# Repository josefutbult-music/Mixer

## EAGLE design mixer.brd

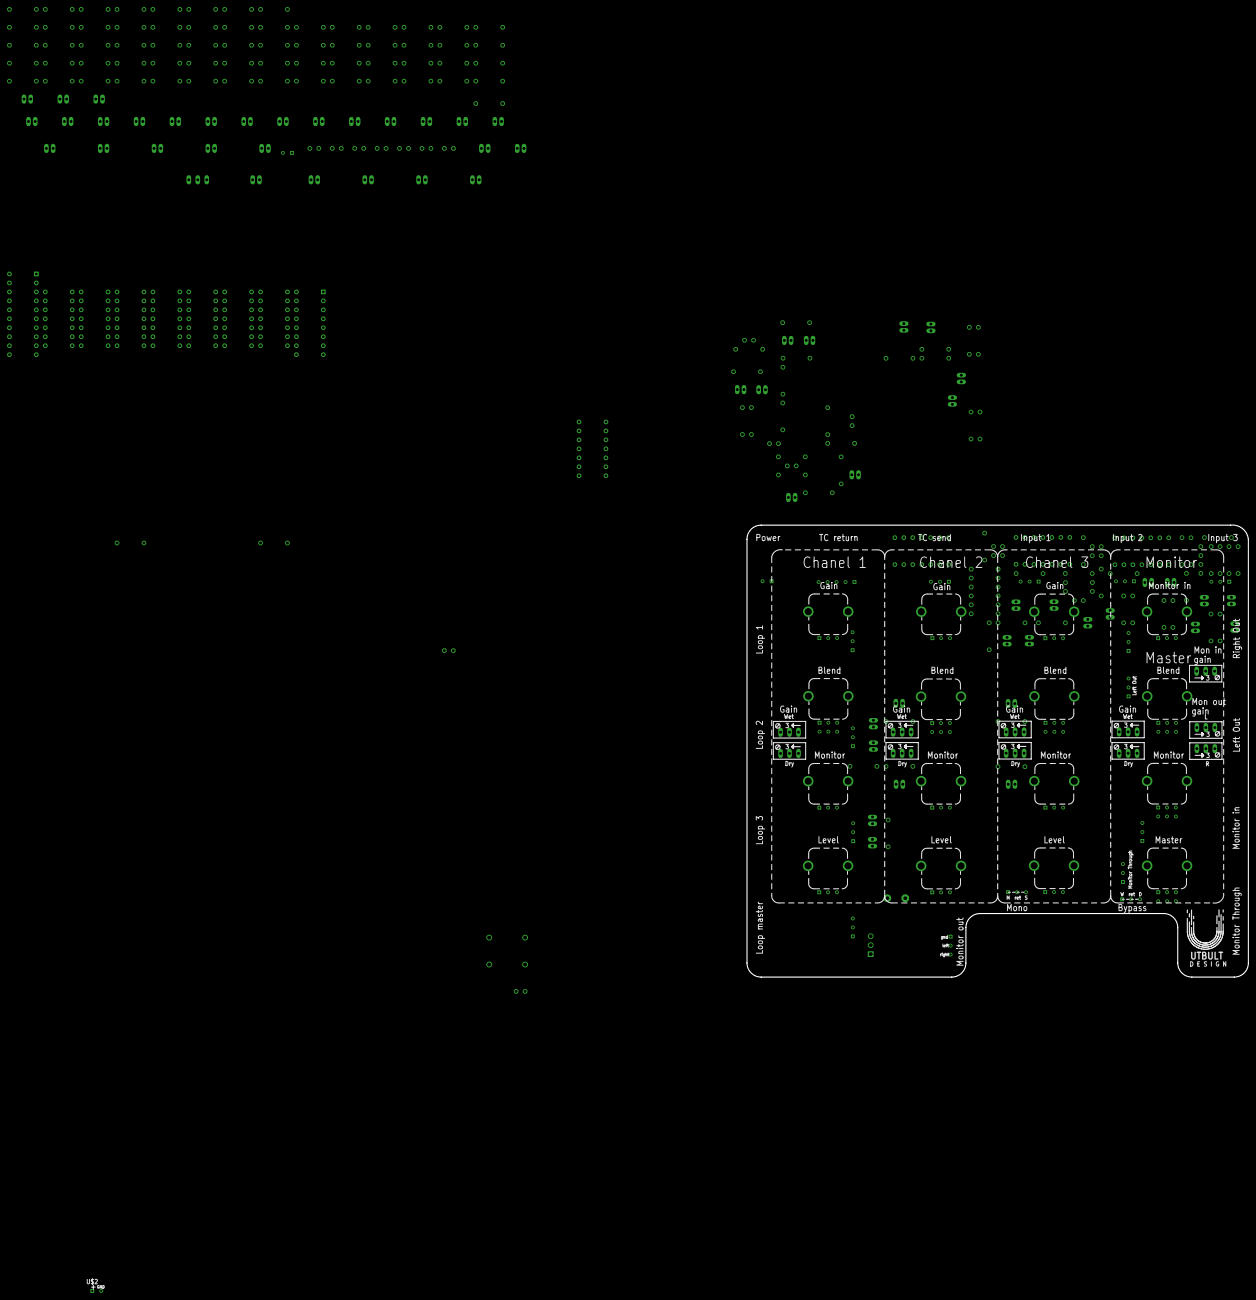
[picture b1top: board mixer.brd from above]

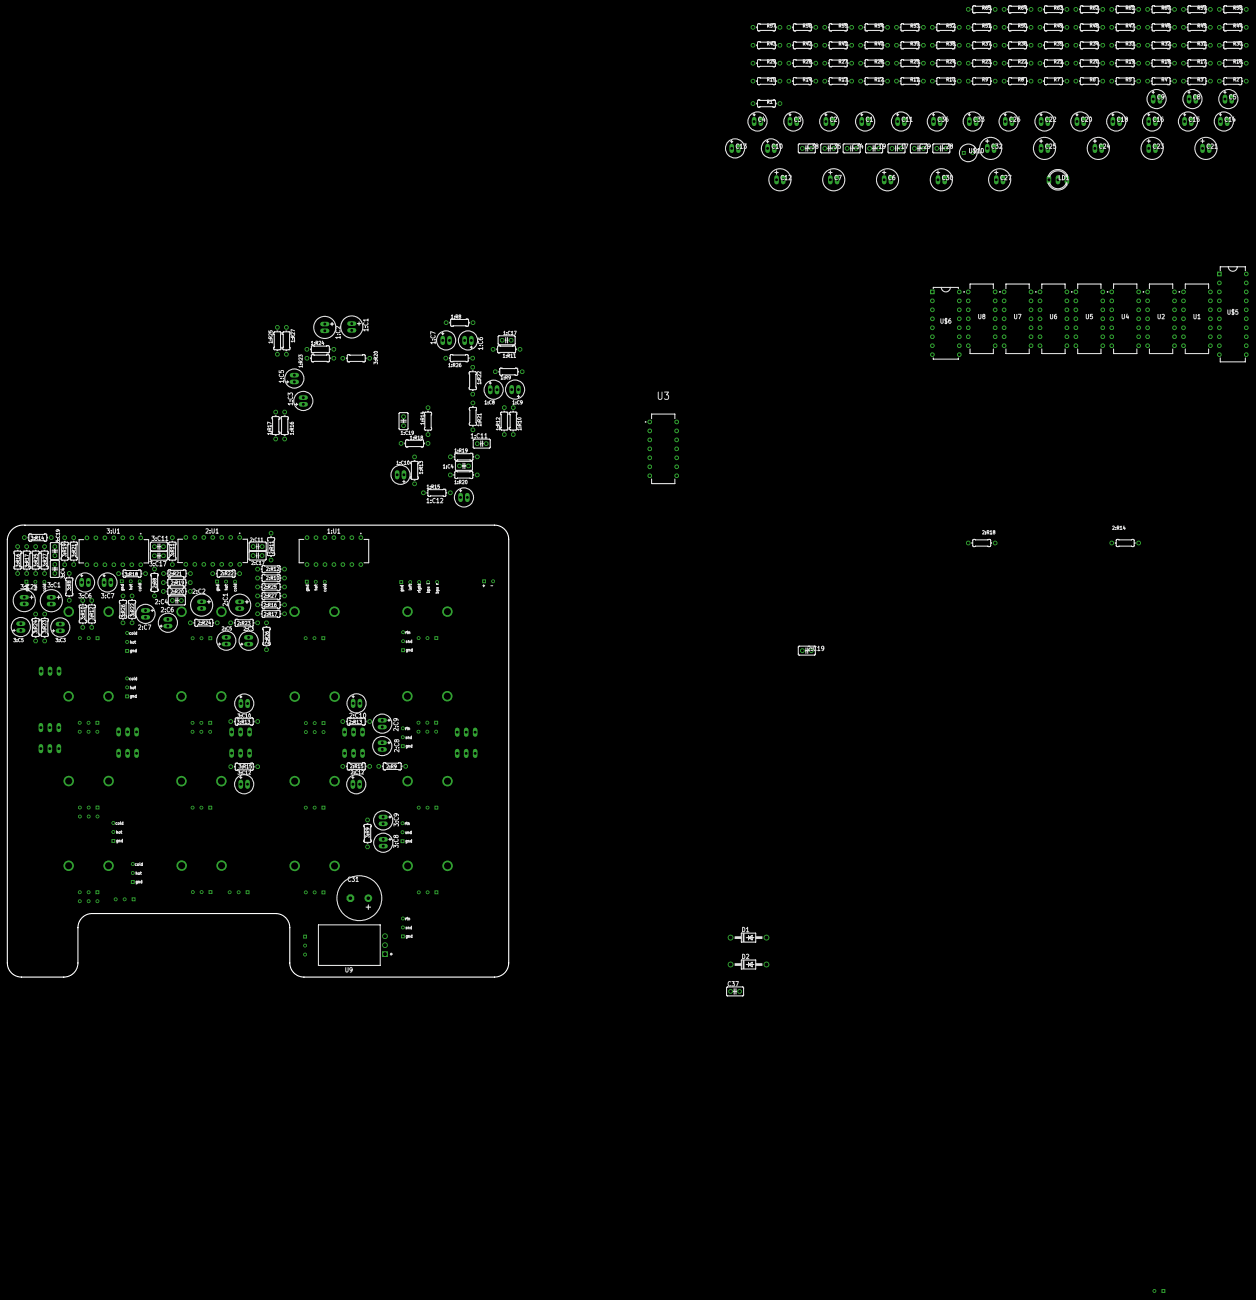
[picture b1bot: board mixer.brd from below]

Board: 2 copper layers, 142.0 x 128.0 mm, 269 parts (237 on the bottom side), 199 nets, no tracks yet.

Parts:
1:BLEND, 2:BLEND, 3:BLEND: 50 k; RK09L124000Z
1:C1, 1:C2, 2:C1, 2:C2, 3:C1, 3:C2: 10u, 63V; E2,0-6
1:C3, 1:C5, 1:C6, 1:C7, 1:C8, 1:C9, 1:C10, 1:C12, 2:C3, 2:C5, 2:C6, 2:C7, 2:C8, 2:C9, 2:C10, 2:C12, 3:C3, 3:C5, 3:C6, 3:C7, 3:C8, 3:C9, 3:C10, 3:C12: 10u; E2,0-5
1:C4, 1:C17, 1:C19, 2:C4, 2:C17, 2:C19, 3:C4, 3:C17, 3:C19: 18 p; C025-025X050
1:C11, 2:C11, 3:C11: 100 n; C025-025X050
1:GAIN, 2:GAIN, 3:GAIN: 10 k; RK09L1140
1:GAIN1, 1:GAIN2, 2:GAIN1, 2:GAIN2, 3:GAIN1, 3:GAIN2: 500 k; RJ9W
1:IN, 2:IN, 3:IN: HOT_COLD
1:LEVEL, 2:LEVEL, 3:LEVEL: RK09L1140
1:R8, 1:R9, 1:R10, 1:R16, 1:R17, 1:R23, 1:R24, 2:R8, 2:R9, 2:R10, 2:R16, 2:R17, 2:R23, 2:R24, 3:R8, 3:R9, 3:R10, 3:R16, 3:R17, 3:R23, 3:R24: 100 k; 0204/7
1:R11, 1:R14, 2:R11, 2:R14, 3:R11, 3:R14: 47 k; 0204/7
1:R12, 1:R18, 1:R26, 2:R12, 2:R18, 2:R26, 3:R12, 3:R18, 3:R26: 1 k; 0204/7
1:R13, 1:R15, 2:R13, 2:R15, 3:R13, 3:R15: 2.2 k; 0204/7
1:R19, 1:R20, 1:R21, 1:R22, 2:R19, 2:R20, 2:R21, 2:R22, 3:R19, 3:R20, 3:R21, 3:R22: 10 k; 0204/7
1:R25, 1:R27, 2:R25, 2:R27, 3:R25, 3:R27: 4.7 k; 0204/7
1:U1, 2:U1, 3:U1: TL074; DIP762W53P254L1969H508Q14B
1:U2, 2:U2, 3:U2: SEND_RETURN; SND_RET
BLEND1: 50 k; RK09L124000Z
BYPASS: BUTTON; 3-HOLES
C1, C2, C3, C4, C5, C8, C9, C10, C11, C13, C14, C15, C16, C18, C20, C22, C26, C33, C36: 10u; E2,0-5
C6, C7, C12, C21, C23, C24, C25, C32: 10u, 63V; E2,0-6
C17, C19, C34, C35, C38: 18 p; C025-025X050
C27, C30: 2.2u, 63V; E2,0-6
C28, C29, C37: 100 n; C025-025X050
C31: 390 u / 63 V; E5,0-12,5
D1, D2: 1N4004; DO41-10
GAIN1, GAIN2, GAIN3, GAIN4: 500 k; RJ9W
GAIN5: 10 k; RJ9W
LD1: DUOLED-A-5MM
LOOPMASTER: SEND_RETURN; SND_RET
MONO: BUTTON; 3-HOLES
MON_IN: HOT_COLD
MON_OUT: LEFT_RIGHT
MON_THROUGH: HOT_COLD
OUT_L: HOT_COLD
OUT_R: HOT_COLD
PWR$1: PWR
R1, R2, R3, R4, R6, R21, R22, R25, R26, R27, R32, R33, R34, R35, R36, R45, R46, R51, R52, R53, R54, R64, R65: 10 k; 0204/7
R5, R7, R28, R29, R37, R38: 100; 0204/7
R8, R9, R10, R16, R17, R19, R20, R23, R24, R30, R31, R39, R40, R47, R48, R49, R50: 100 k; 0204/7
R11, R14, R55, R61: 47 k; 0204/7
R12, R18, R56, R60, R63: 1 k; 0204/7
R13, R15, R59, R62: 2.2 k; 0204/7
R41, R42, R43, R44, R57, R58: 4.7 k; 0204/7
TC_RET: LEFT_RIGHT_BYPASS
TC_SEND_JACK: HOT_COLD
U1, U2, U3, U4, U5, U6, U7, U8: TL074; DIP762W53P254L1969H508Q14B
U9: V7809W-500R; CONV_V7809W-500R
U$1: UTBULT_DESIGN3; UD_3
U$2: UNBALANCED_INPUT_JACK; BALANCED_INPUT_JACK
U$5: ADG333ABNZADG333ABNZ; DIP762W53P254L2591H508Q20B
U$6: ADG436BNZADG436BNZ; DIP762W53P254L2006H508Q16B
U$10: SBC1-102-211
VOLUM6: 50 k; RK09L124000Z
VOLUME1: 50 k; RK09L124000Z
VOLUME2, VOLUME3, VOLUME4, VOLUME5: 10 k; RK09L1140

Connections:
1:COLD_IN: 1:C1.+, 1:IN.P$3, 1:R27.2
1:COLD_SEND: 1:C3.+, 1:R16.2, 1:U1.10
1:HOT_IN: 1:C2.+, 1:IN.P$2, 1:R25.2
1:HOT_SEND: 1:C5.+, 1:R17.2, 1:U1.12
1:N$1: 1:C10.+, 1:R13.2
1:N$2: 1:C12.+, 1:R15.2
1:N$3: 1:GAIN1.A, 1:GAIN1.S, 1:R13.1
1:N$4: 1:GAIN2.A, 1:GAIN2.S, 1:R15.1
1:N$9: 1:GAIN.P$3, 1:R19.2, 1:R20.2, 1:R21.1, 1:U1.8, 1:U1.9
1:N$11: 1:C4.1, 1:R19.1
1:N$12: 1:C4.2, 1:R20.1, 1:R22.2, 1:R26.1, 1:U1.13
1:N$14: 1:C1.-, 1:C3.-, 1:R23.2
1:N$15: 1:C2.-, 1:C5.-, 1:R24.2
1:N$17: 1:GAIN.P$2, 1:R26.2
1:N$23: 1:C6.-, 1:C7.-, 1:R8.2
1:N$24: 1:C11.1, 1:U1.11
1:N$25: 1:C6.+, 1:U2.P$3
1:N$26: 1:C8.-, 1:C9.-, 1:R9.2
1:N$27: 1:C8.+, 1:U2.P$2
1:N$28: 1:C9.+, 1:R10.2, 1:R12.2
1:N$29: 1:C17.2, 1:GAIN1.E, 1:R11.2, 1:U1.2
1:N$30: 1:C19.2, 1:GAIN2.E, 1:R14.2, 1:U1.6
1:N$33: 1:R12.1, 1:U1.3
1:N$36: 1:R18.1, 1:U1.5
1:N$37: 1:BLEND.P$8, 1:C19.1, 1:R14.1, 1:U1.7
1:SND_RET_OUT: 1:BLEND.P$1, 1:C17.1, 1:R11.1, 1:U1.1
2:COLD_IN: 2:C1.+, 2:IN.P$3, 2:R27.2
2:COLD_SEND: 2:C3.+, 2:R16.2, 2:U1.10
2:HOT_IN: 2:C2.+, 2:IN.P$2, 2:R25.2
2:HOT_SEND: 2:C5.+, 2:R17.2, 2:U1.12
2:N$1: 2:C10.+, 2:R13.2
2:N$2: 2:C12.+, 2:R15.2
2:N$3: 2:GAIN1.A, 2:GAIN1.S, 2:R13.1
2:N$4: 2:GAIN2.A, 2:GAIN2.S, 2:R15.1
2:N$9: 2:GAIN.P$3, 2:R19.2, 2:R20.2, 2:R21.1, 2:U1.8, 2:U1.9
2:N$11: 2:C4.1, 2:R19.1
2:N$12: 2:C4.2, 2:R20.1, 2:R22.2, 2:R26.1, 2:U1.13
2:N$14: 2:C1.-, 2:C3.-, 2:R23.2
2:N$15: 2:C2.-, 2:C5.-, 2:R24.2
2:N$17: 2:GAIN.P$2, 2:R26.2
2:N$23: 2:C6.-, 2:C7.-, 2:R8.2
2:N$24: 2:C11.1, 2:U1.11
2:N$25: 2:C6.+, 2:U2.P$3
2:N$26: 2:C8.-, 2:C9.-, 2:R9.2
2:N$27: 2:C8.+, 2:U2.P$2
2:N$28: 2:C9.+, 2:R10.2, 2:R12.2
2:N$29: 2:C17.2, 2:GAIN1.E, 2:R11.2, 2:U1.2
2:N$30: 2:C19.2, 2:GAIN2.E, 2:R14.2, 2:U1.6
2:N$33: 2:R12.1, 2:U1.3
2:N$36: 2:R18.1, 2:U1.5
2:N$37: 2:BLEND.P$8, 2:C19.1, 2:R14.1, 2:U1.7
2:SND_RET_OUT: 2:BLEND.P$1, 2:C17.1, 2:R11.1, 2:U1.1
3:COLD_IN: 3:C1.+, 3:IN.P$3, 3:R27.2
3:COLD_SEND: 3:C3.+, 3:R16.2, 3:U1.10
3:HOT_IN: 3:C2.+, 3:IN.P$2, 3:R25.2
3:HOT_SEND: 3:C5.+, 3:R17.2, 3:U1.12
3:N$1: 3:C10.+, 3:R13.2
3:N$2: 3:C12.+, 3:R15.2
3:N$3: 3:GAIN1.A, 3:GAIN1.S, 3:R13.1
3:N$4: 3:GAIN2.A, 3:GAIN2.S, 3:R15.1
3:N$9: 3:GAIN.P$3, 3:R19.2, 3:R20.2, 3:R21.1, 3:U1.8, 3:U1.9
3:N$11: 3:C4.1, 3:R19.1
3:N$12: 3:C4.2, 3:R20.1, 3:R22.2, 3:R26.1, 3:U1.13
3:N$14: 3:C1.-, 3:C3.-, 3:R23.2
3:N$15: 3:C2.-, 3:C5.-, 3:R24.2
3:N$17: 3:GAIN.P$2, 3:R26.2
3:N$23: 3:C6.-, 3:C7.-, 3:R8.2
3:N$24: 3:C11.1, 3:U1.11
3:N$25: 3:C6.+, 3:U2.P$3
3:N$26: 3:C8.-, 3:C9.-, 3:R9.2
3:N$27: 3:C8.+, 3:U2.P$2
3:N$28: 3:C9.+, 3:R10.2, 3:R12.2
3:N$29: 3:C17.2, 3:GAIN1.E, 3:R11.2, 3:U1.2
3:N$30: 3:C19.2, 3:GAIN2.E, 3:R14.2, 3:U1.6
3:N$33: 3:R12.1, 3:U1.3
3:N$36: 3:R18.1, 3:U1.5
3:N$37: 3:BLEND.P$8, 3:C19.1, 3:R14.1, 3:U1.7
3:SND_RET_OUT: 3:BLEND.P$1, 3:C17.1, 3:R11.1, 3:U1.1
+9V: 1:C11.2, 1:U1.4, 2:C11.2, 2:U1.4, 3:C11.2, 3:U1.4, C29.1, D1.C, D2.C, R45.1, R64.2, R65.1, U1.4, U2.4, U3.4, U4.4, U5.4, U6.4, U7.4, U8.4, U$5.VDD, U$6.VDD
+48V: 1:R25.1, 1:R27.1, 2:R25.1, 2:R27.1, 3:R25.1, 3:R27.1, C30.+, C31.+, R41.1, R42.1, R43.1, R44.1, R57.1, R58.1, U$10.P$2
COLD_SEND: C11.+, R47.2, U4.3
DRY1: 1:C7.+, 1:R18.2, 1:R22.1, 1:U1.14, U$5.S1B, VOLUME2.P$3
DRY2: 2:C7.+, 2:R18.2, 2:R22.1, 2:U1.14, U$5.S2B, VOLUME3.P$3
DRY3: 3:C7.+, 3:R18.2, 3:R22.1, 3:U1.14, U$5.S3B, VOLUME4.P$3
GND: 1:BLEND.P$4, 1:BLEND.P$5, 1:C10.-, 1:C12.-, 1:GAIN.P$4, 1:GAIN.P$5, 1:IN.P$1, 1:LEVEL.P$4, 1:LEVEL.P$5, 1:R8.1, 1:R9.1, 1:R23.1, 1:R24.1, 1:U2.P$1, 2:BLEND.P$4, 2:BLEND.P$5, 2:C10.-, 2:C12.-, 2:GAIN.P$4, 2:GAIN.P$5, 2:IN.P$1, 2:LEVEL.P$4, 2:LEVEL.P$5, 2:R8.1, 2:R9.1, 2:R23.1, 2:R24.1, 2:U2.P$1, 3:BLEND.P$4, 3:BLEND.P$5, 3:C10.-, 3:C12.-, 3:GAIN.P$4, 3:GAIN.P$5, 3:IN.P$1, 3:LEVEL.P$4, 3:LEVEL.P$5, 3:R8.1, 3:R9.1, 3:R23.1, 3:R24.1, 3:U2.P$1, BLEND1.P$4, BLEND1.P$5, BYPASS.P$3, C18.-, C20.-, C27.-, C28.2, C29.2, C30.-, C31.-, C33.-, C36.-, C37.2, LD1.A, LOOPMASTER.P$1, MON_IN.P$1, MON_OUT.P$1, MON_THROUGH.P$1, OUT_L.P$1, OUT_R.P$1, PWR$1.P$2, R8.1, R9.1, R16.1, R19.1, R23.1, R24.1, R30.1, R31.1, R39.1, R40.1, R46.2, R49.1, R50.1, TC_RET.GND, TC_SEND_JACK.P$1, U1.11, U2.11, U3.11, U4.11, U5.11, U6.11, U7.11, U8.11, U9.2, U$2.GND, U$5.GND, U$5.VSS, U$6.GND, U$6.VSS, VOLUM6.P$4, VOLUM6.P$5, VOLUME1.P$4, VOLUME1.P$5, VOLUME2.P$4, VOLUME2.P$5, VOLUME3.P$4, VOLUME3.P$5, VOLUME4.P$4, VOLUME4.P$5, VOLUME5.P$4, VOLUME5.P$5
HOT_SEND: C26.+, R48.2, U4.5
L_COLD: C12.+, OUT_L.P$3, R41.2
L_HOT: C21.+, OUT_L.P$2, R42.2
MASTER_MON_L: U$6.D2, VOLUM6.P$3, VOLUME1.P$8
MASTER_MON_R: U$6.D1, VOLUM6.P$8, VOLUME1.P$3
MIX1: 1:LEVEL.P$2, U1.3
MIX2: 2:LEVEL.P$2, U1.5
MIX3: 3:LEVEL.P$2, U1.10
MIX_OUT: C14.-, R8.2, R18.2, U1.13, U1.14, U8.3, U8.5
MON: R53.1, U4.7, VOLUME5.P$3
MON_COLD: C25.+, MON_IN.P$3, MON_THROUGH.P$3, R58.2
MON_HOT: C32.+, MON_IN.P$2, MON_THROUGH.P$2, R57.2
MON_OUT_L: C35.1, MON_OUT.P$2, R55.1, U7.1
MON_OUT_R: C38.1, MON_OUT.P$3, R61.1, U7.7
unnamed: R1.1, R2.2, U2.9
unnamed: R6.1, U2.10
unnamed: R1.2, R5.2, U2.8
unnamed: U1.1, U1.2, U1.6, U1.7, U1.8, U1.9, U1.12
unnamed: R3.1, R4.2, U2.13
unnamed: R4.1, R7.2, U2.14
unnamed: C8.+, R5.1
unnamed: C9.+, R7.1
unnamed: C1.-, C3.-, R16.2
unnamed: R21.1, U3.3
unnamed: C2.-, C4.-, R19.2
unnamed: R22.2, R28.2, U3.1
unnamed: C6.-, C8.-, R23.2
unnamed: C7.-, C9.-, R24.2
unnamed: R22.1, R25.2, U3.2
unnamed: R26.1, R27.2, U3.6
unnamed: R27.1, R29.2, U3.7
unnamed: C5.-, C21.-, R30.2
unnamed: C10.-, C12.-, R31.2
unnamed: C5.+, R28.1
unnamed: C10.+, R29.1
unnamed: GAIN1.A, GAIN1.S, R13.1
unnamed: R32.1, U3.10
unnamed: C11.-, C25.-, R49.2
unnamed: C15.-, C16.-, R9.2
unnamed: C26.-, C32.-, R50.2
unnamed: C16.+, R10.2, R12.2
unnamed: C17.2, GAIN1.E, R11.2, U2.2
unnamed: C19.2, GAIN2.E, R14.2, U2.6
unnamed: GAIN2.A, GAIN2.S, R15.1
unnamed: C18.+, R13.2
unnamed: R12.1, U2.3
unnamed: GAIN4.A, GAIN4.S, R62.1
unnamed: C20.+, R15.2
unnamed: R18.1, U2.5
unnamed: BLEND1.P$8, C19.1, R14.1, U2.7
unnamed: R33.2, R37.2, U3.8
unnamed: R33.1, R34.2, U3.9
unnamed: R35.1, R36.2, U3.13
unnamed: R36.1, R38.2, U3.14
unnamed: C13.-, C23.-, R39.2
unnamed: C22.-, C24.-, R40.2
unnamed: C13.+, R37.1
unnamed: C22.+, R38.1
unnamed: GAIN5.E, R51.2, R52.2, R54.1, U4.1, U4.2
unnamed: C34.1, R51.1
unnamed: C34.2, R52.1, R53.2, R56.1, U4.6
unnamed: U4.8, U4.9, U6.1, U6.2, U6.10
unnamed: GAIN5.S, R56.2
unnamed: MONO.P$1, U6.3, VOLUM6.P$2
unnamed: U4.13, U4.14, U6.6, U6.7, U6.12
unnamed: U5.3, VOLUME2.P$2
unnamed: U5.5, VOLUME3.P$2
unnamed: U5.10, VOLUME4.P$2
unnamed: U5.12, VOLUME5.P$2
unnamed: U4.10, U4.12, U5.1, U5.2, U5.6, U5.7, U5.8, U5.9, U5.13, U5.14
unnamed: MONO.P$2, U6.5
unnamed: R63.2, U6.13, U6.14
unnamed: R60.2, U6.8, U6.9
unnamed: GAIN3.A, GAIN3.S, R59.1
unnamed: C33.+, R59.2
unnamed: R60.1, U7.3
unnamed: U8.1, U8.2, U$6.S1B
unnamed: C38.2, GAIN4.E, R61.2, U7.6
unnamed: C35.2, GAIN3.E, R55.2, U7.2
unnamed: C36.+, R62.2
unnamed: R63.1, U7.5
unnamed: D1.A, U9.3
unnamed: U8.6, U8.7, U$6.S2B
unnamed: MONO.P$3, VOLUM6.P$7
unnamed: C28.1, R45.2, R46.1, U7.12
unnamed: LD1.CR, U$5.S4B
unnamed: LD1.CX, U$5.S4A
unnamed: R64.1, U$5.D4
unnamed: C27.+, U9.1, U$10.P$1
unnamed: D2.A, PWR$1.P$1
OUT_L: R21.2, R26.2, VOLUME1.P$7
OUT_R: R32.2, R35.2, VOLUME1.P$2
RET: C15.+, LOOPMASTER.P$2
RET1: 1:LEVEL.P$3, U$5.D1
RET2: 2:LEVEL.P$3, U$5.D2
RET3: 3:LEVEL.P$3, U$5.D3
R_COLD: C24.+, OUT_R.P$3, R43.2
R_HOT: C23.+, OUT_R.P$2, R44.2
SELECT: BYPASS.P$2, R65.2, U$2.HOT, U$5.IN1, U$5.IN2, U$5.IN3, U$5.IN4, U$6.IN1, U$6.IN2
SND: C14.+, LOOPMASTER.P$3
SND_RET_OUT: BLEND1.P$1, C17.1, R11.1, U2.1
TC_BALANCED: BLEND1.P$2, BLEND1.P$7, R3.2, R6.2, U8.10, U8.12
TC_BYPASS_L: TC_RET.BPSR, U8.8, U8.9
TC_BYPASS_R: TC_RET.BPSL, U8.13, U8.14
TC_COLD: C7.+, TC_SEND_JACK.P$3
TC_HOT: C6.+, TC_SEND_JACK.P$2
TC_RET_L: C1.+, TC_RET.LEFT
TC_RET_R: C2.+, TC_RET.RIGHT
TC_WET_L: C3.+, R17.2, U$6.S1A
TC_WET_R: C4.+, R20.2, U$6.S2A
VDD: 1:BLEND.P$3, 1:BLEND.P$6, 1:LEVEL.P$1, 1:R10.1, 1:R16.1, 1:R17.1, 1:R21.2, 2:BLEND.P$3, 2:BLEND.P$6, 2:LEVEL.P$1, 2:R10.1, 2:R16.1, 2:R17.1, 2:R21.2, 3:BLEND.P$3, 3:BLEND.P$6, 3:LEVEL.P$1, 3:R10.1, 3:R16.1, 3:R17.1, 3:R21.2, BLEND1.P$3, BLEND1.P$6, C37.1, R2.1, R10.1, R17.1, R20.1, R25.1, R34.1, R47.1, R48.1, R54.2, U2.12, U3.5, U3.12, U7.13, U7.14, VOLUM6.P$1, VOLUM6.P$6, VOLUME1.P$1, VOLUME1.P$6, VOLUME2.P$1, VOLUME3.P$1, VOLUME4.P$1, VOLUME5.P$1
WET1: 1:BLEND.P$2, 1:BLEND.P$7, U$5.S1A
WET2: 2:BLEND.P$2, 2:BLEND.P$7, U$5.S2A
WET3: 3:BLEND.P$2, 3:BLEND.P$7, U$5.S3A

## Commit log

2020-10-19 Init
2020-10-19 Added png diagra
2020-11-08 Started board layout and removed EQ
2020-11-08 Added internal bondary
2020-11-28 Swapped gain trimpots and started restructuring
